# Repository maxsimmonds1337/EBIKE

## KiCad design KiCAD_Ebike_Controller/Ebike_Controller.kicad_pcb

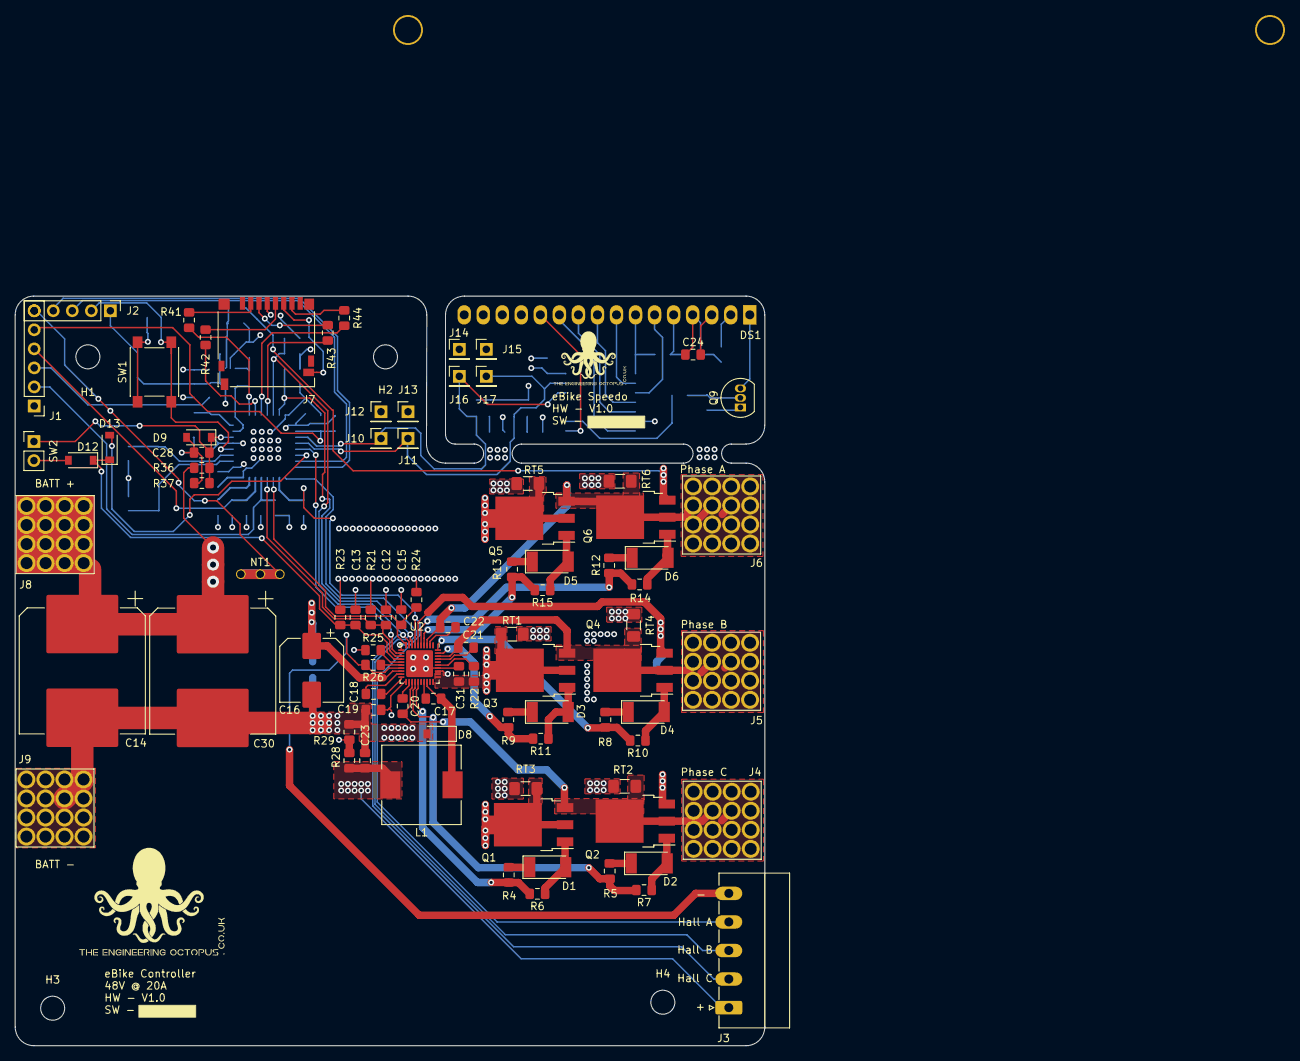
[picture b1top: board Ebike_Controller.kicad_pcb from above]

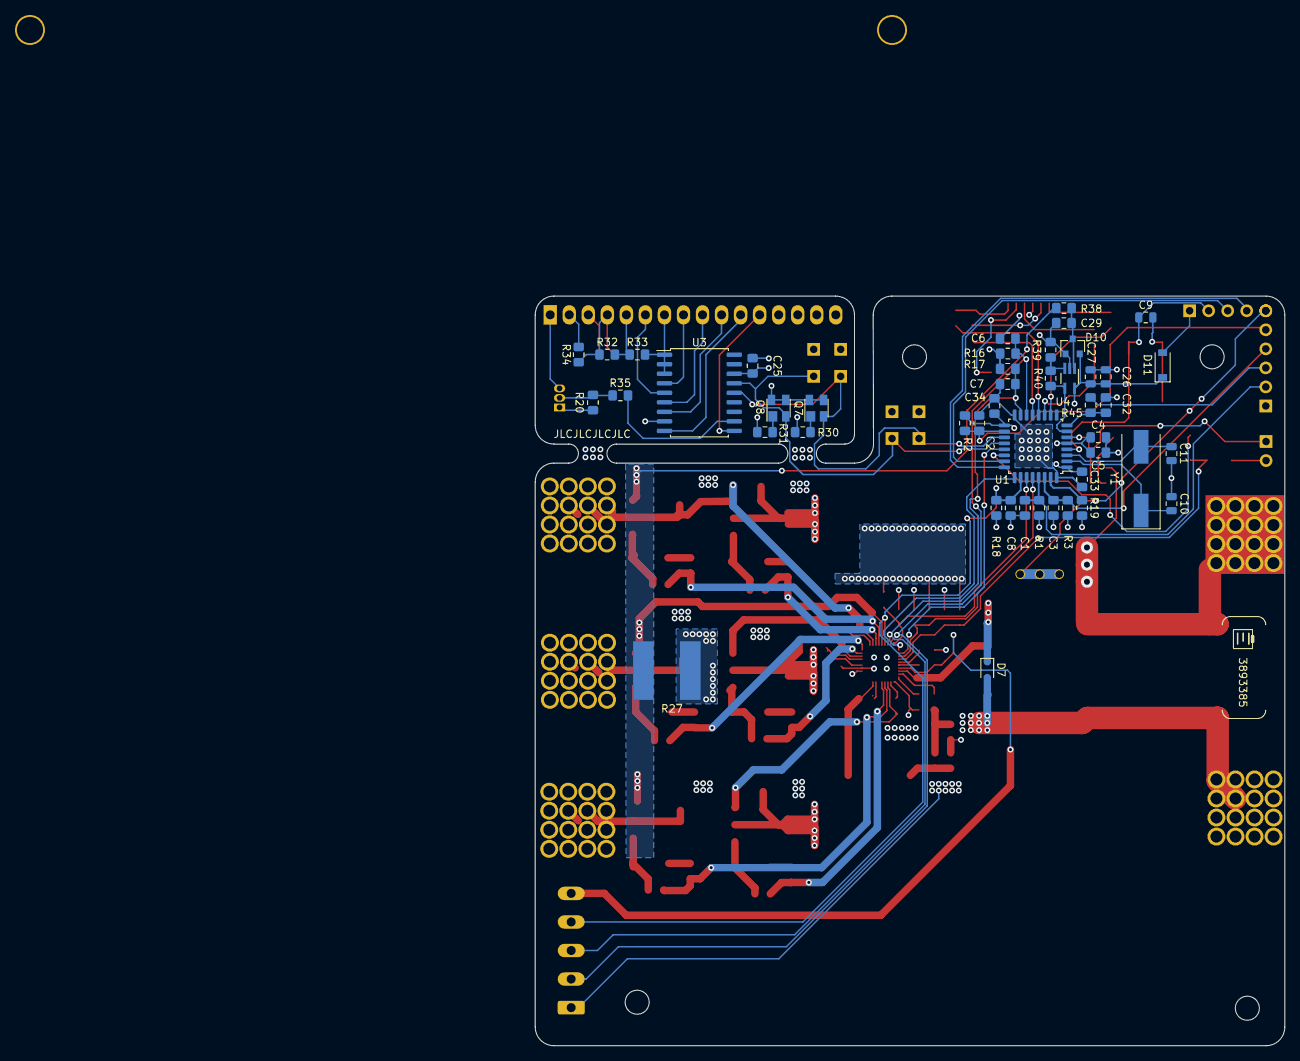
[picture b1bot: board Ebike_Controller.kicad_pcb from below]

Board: 4 copper layers, 100.0 x 100.0 mm, 138 parts (46 on the bottom side), 88 nets.

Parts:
C1, C2, C3, C5, C6, C7, C8, C12, C13, C15, C24, C25, C31, C33, C34: 100n; C_0805_2012Metric_Pad1.15x1.40mm_HandSolder
C4, C17, C19: 10u; C_0805_2012Metric_Pad1.15x1.40mm_HandSolder
C9: 100n; C_0805_2012Metric
C10, C11: 10p; C_0805_2012Metric
C14: 470u; CP_Elec_16x17.5
C16: 47u; CP_Elec_8x10
C18, C20, C21, C22: 0.47n; C_0805_2012Metric_Pad1.15x1.40mm_HandSolder
C23: 22u; C_0805_2012Metric_Pad1.15x1.40mm_HandSolder
C26: 10u; C_0805_2012Metric
C27: 10n; C_0805_2012Metric
C28, C29, C32: 50n; C_0805_2012Metric_Pad1.15x1.40mm_HandSolder
C30: 100u; CP_Elec_16x17.5
D1, D2, D3, D4, D5, D6: SM4007; D_MELF
D7: BZX384C56; D_SOD-323
D8, D11, D12, D13: STPS2L60ZFY; D_SOD-123
D9: BZT52C3V6; D_SOD-123
D10: BAS40-04; SOT-23
DS1: HY1602E
H1, H2: MountingHole; MountingHole_3.2mm_M3
H3, H4: MountingHole; MountingHole_3.2mm_M3_DIN965
J1: IO; PinHeader_1x06_P2.54mm_Vertical
J2: Prog; PinHeader_1x05_P2.54mm_Vertical
J3: Hall Effect Sensors; PhoenixContact_MC_1,5_5-G-3.81_1x05_P3.81mm_Horizontal
J4: PHASE_A; 180A_screw_terminal_7461383
J5: PHASE_B; 180A_screw_terminal_7461383
J6: PHASE_C; 180A_screw_terminal_7461383
J7: Micro_SD_Card; microSD_HC_Hirose_DM3D-SF
J8: +48V; 180A_screw_terminal_7461383
J9: GND; 180A_screw_terminal_7461383
J10: I2C_SCL; PinHeader_1x01_P2.54mm_Vertical
J11: I2C_SDA; PinHeader_1x01_P2.54mm_Vertical
J12: +3V3; PinHeader_1x01_P2.54mm_Vertical
J13: GNDD; PinHeader_1x01_P2.54mm_Vertical
J14: +3V3_S; PinHeader_1x01_P2.54mm_Vertical
J15: GNDD_S; PinHeader_1x01_P2.54mm_Vertical
J16: I2C_SCL_S; PinHeader_1x01_P2.54mm_Vertical
J17: I2C_SDA_S; PinHeader_1x01_P2.54mm_Vertical
L1: 100u; L_10.4x10.4_H4.8
NT1: Net-Tie_3; NetTie-3_THT_Pad1.0mm
Q1, Q2, Q3, Q4, Q5, Q6: DMT10H010LK3; TO-252-3_TabPin2
Q7, Q8: BCV62; SOT-143
Q9: 2N7000; TO-92_Inline
R1, R2, R3, R16, R17, R18, R19, R20, R22, R25: 100k; R_0805_2012Metric_Pad1.15x1.40mm_HandSolder
R4, R5, R6, R7, R8, R9, R10, R11, R12, R13, R14, R15: 5; R_0805_2012Metric_Pad1.15x1.40mm_HandSolder
R21, R23, R24, R37: 10k; R_0805_2012Metric_Pad1.15x1.40mm_HandSolder
R26, R32, R33: 50k; R_0805_2012Metric_Pad1.15x1.40mm_HandSolder
R27: 20m; 20m_4W
R28: 49k9; R_0805_2012Metric_Pad1.15x1.40mm_HandSolder
R29: 23k7; R_0805_2012Metric_Pad1.15x1.40mm_HandSolder
R30, R31: 4k7; R_0805_2012Metric_Pad1.15x1.40mm_HandSolder
R34: 220; R_0805_2012Metric_Pad1.15x1.40mm_HandSolder
R35: 20; R_0805_2012Metric_Pad1.15x1.40mm_HandSolder
R36: 180k; R_0805_2012Metric_Pad1.15x1.40mm_HandSolder
R38, R45: 8.2k; R_0805_2012Metric_Pad1.15x1.40mm_HandSolder
R39: 9.1k; R_0805_2012Metric_Pad1.15x1.40mm_HandSolder
R40: 47k; R_0805_2012Metric_Pad1.15x1.40mm_HandSolder
R41, R42, R43, R44: 0R; R_0805_2012Metric_Pad1.15x1.40mm_HandSolder
RT1, RT2, RT3, RT4, RT5, RT6: R_Thermal; R_1206_3216Metric_Pad1.42x1.75mm_HandSolder
SW1: SW_Push; SW_Push_1P1T_NO_6x6mm_H9.5mm
SW2: SW_SPST; PinHeader_1x02_P2.54mm_Vertical
U1: STM32F030K6Tx; LQFP-32_7x7mm_P0.8mm
U2: MP6535; QFN-40-1EP_5x5mm_P0.4mm_EP3.6x3.6mm
U3: PCF8574; SOIC-18W_7.5x11.6mm_P1.27mm
U4: MCP6V61U; SOT-353_SC-70-5_Handsoldering
Y1: Crystal; Crystal_SMD_HC49-SD

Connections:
+48V: C14.1, C16.1, C30.1, C31.1, D7.1, J8.1, Q1.2, Q3.2, Q5.2, R22.1, R36.1, RT1.1, RT3.1, RT5.1, U2.18, U2.31, U2.32
/+3.3V: C4.1, C5.1, C23.1, C24.1, C25.1, C26.1, C27.1, C33.1, C34.1, D10.2, D11.1, DS1.4, J1.1, J3.1, J7.4, J12.1, J14.1, L1.2, Q7.3, Q7.4, Q8.3, Q8.4, R1.2, R2.2, R3.2, R16.1, R17.1, R18.1, R21.1, R23.1, R24.1, R28.1, R32.1, R34.1, U1.1, U1.5, U1.17, U3.16, U4.5
/BLDC Driver/DIR_PA1: U1.21, U2.12
/BLDC Driver/HA: C6.1, J3.2, R16.2, U1.14, U2.9
/BLDC Driver/PA1: R4.2, R6.2, U2.25
/BLDC Driver/PA3: R5.2, R7.2, U2.24
/BLDC Driver/PB1: R9.2, R11.2, U2.39
/BLDC Driver/PB3: R8.2, R10.2, U2.40
/BLDC Driver/PC1: R13.2, R15.2, U2.4
/BLDC Driver/PC3: R12.2, R14.1, U2.5
/BLDC Driver/PWM_PA0: U1.25, U2.11
/BLDC Driver/VREG: C19.1, R25.1, U2.21
/BLDC Driver/nBRAKE_PA3: C15.1, R24.2, U1.27, U2.10
/BLDC Driver/nFAULT: C12.1, R21.2, U1.28, U2.13
/BLDC Driver/nSLEEP_PA12: C13.1, D12.1, D13.1, R23.2, U2.14
/BMS/I_BATT_MON_PA1: R40.1, U1.7, U4.4
/BMS/V_BATT_MON_PA0: C28.1, D9.1, R36.2, R37.1, SW2.1, U1.6
/BRAKE_SW_BP6: C1.1, J1.2, R1.1, U1.29
/LCD/LCD_I2C1: J10.1, J16.1, Q7.2, U1.19, U3.14
/LCD/LCD_I2C2: J11.1, J17.1, Q8.2, U1.20, U3.15
/LSS: Q2.3, Q4.3, Q6.3, R27.1, R38.1, U2.6
/MCU/HALL_B_PB1: C7.1, J3.3, R17.2, U1.15, U2.8
/MCU/HALL_C_PB3: C8.1, J3.4, R18.2, U1.26, U2.7
/MCU/SD_SPI1: R41.2, U1.10
/MCU/SD_SPI2: R42.2, U1.11
/MCU/SD_SPI3: R44.1, U1.12
/MCU/SD_SPI4: R43.2, U1.13
/MCU/THROTTLE_PA2: C32.1, R45.2, U1.8
/MCU/nSLEEP_PA12: D13.2, U1.22
/MODE1_SW_PB7: C3.1, J1.4, R3.1, U1.30
/MODE2_SW_PA3: C2.1, J1.5, R2.1, U1.18
/SWCLK: J2.4, U1.24
/SWDIO: J2.3, U1.23
/THROTTLE_PA2: J1.3, R45.1
/Triple_H_Bridge/PHASE_A: C20.2, J4.1, Q1.3, Q2.2, RT2.1, U2.23
/Triple_H_Bridge/PHASE_B: C21.2, J5.1, Q3.3, Q4.2, RT4.1, U2.38
/Triple_H_Bridge/PHASE_C: C22.2, J6.1, Q5.3, Q6.2, RT6.1, U2.3
/nRST: C9.1, J2.2, SW1.1, U1.4
GND: C14.2, C16.2, C19.2, C23.2, C30.2, C31.2, D7.2, D8.2, J9.1, NT1.2, R27.2, R29.2, RT1.2, RT2.2, RT3.2, RT4.2, RT5.2, RT6.2, U2.34, U2.41
GNDA: C1.2, C2.2, C3.2, C4.2, C5.2, C6.2, C7.2, C8.2, C9.2, C10.2, C11.2, C26.2, C27.2, C28.2, C29.2, C32.2, C33.2, C34.2, D9.2, D10.1, NT1.1, R19.2, R37.2, R39.1, SW1.2, U1.16, U1.32, U4.2
GNDD: C12.2, C13.2, C15.2, C24.2, C25.2, DS1.3, DS1.7, J1.6, J2.5, J3.5, J7.6, J7.9, J13.1, J15.1, NT1.3, Q9.1, R20.2, R26.2, R30.2, R31.2, R33.2, U2.17, U3.1, U3.2, U3.3, U3.8
unnamed: C10.1, U1.2, Y1.1
unnamed: C11.1, U1.3, Y1.2
unnamed: C17.1, D8.1, L1.1, U2.28
unnamed: C17.2, U2.27
unnamed: C18.1, U2.19
unnamed: C18.2, U2.20
unnamed: C20.1, U2.22
unnamed: C21.1, U2.37
unnamed: C22.1, U2.2
unnamed: C29.1, D10.3, R38.2, U4.1
unnamed: D1.1, R4.1
unnamed: D1.2, Q1.1, R6.1
unnamed: D2.1, R5.1
unnamed: D2.2, Q2.1, R7.1
unnamed: D3.1, R9.1
unnamed: D3.2, Q3.1, R11.1
unnamed: D4.1, R8.1
unnamed: D4.2, Q4.1, R10.1
unnamed: D5.1, R13.1
unnamed: D5.2, Q5.1, R15.1
unnamed: D6.1, R12.1
unnamed: D6.2, Q6.1, R14.2
unnamed: D11.2, J2.1
unnamed: D12.2, SW2.2
unnamed: DS1.1, Q9.3
unnamed: DS1.2, R34.2
unnamed: DS1.5, R32.2, R33.1
unnamed: DS1.6, U3.5
unnamed: DS1.8, U3.4
unnamed: DS1.9, U3.6
unnamed: DS1.10, U3.7
unnamed: DS1.11, U3.9
unnamed: DS1.12, U3.10
unnamed: J7.2, R41.1
unnamed: J7.3, R43.1
unnamed: J7.5, R42.1
unnamed: J7.7, R44.2
unnamed: Q7.1, R30.1
unnamed: Q8.1, R31.1
unnamed: Q9.2, R20.1, R35.1
unnamed: R19.1, U1.31
unnamed: R22.2, U2.35
unnamed: R25.2, U2.15
unnamed: R26.1, U2.16
unnamed: R28.2, R29.1, U2.33
unnamed: R35.2, U3.11
unnamed: R39.2, R40.2, U4.3

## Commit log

2020-10-28 Started the schematic
2020-11-03 close to being done, need to add current pull ups on i2c
2020-11-19 schem done
2020-11-24 adding footprints
2021-01-02 50% of the way through the layout
2021-01-07 Layout done. will tidy up ref des next
2021-01-08 Finished ready for fab
2021-01-10 done and gerbes sent to JLC
2021-01-10 Added JLC serial number and my logo
2021-01-10 replotted the gerbers, sedning to JLC
2021-01-10 saved gerbers as zip
2021-01-11 added a bom, this is the last commit on this branch
2021-09-16 updating the repo
